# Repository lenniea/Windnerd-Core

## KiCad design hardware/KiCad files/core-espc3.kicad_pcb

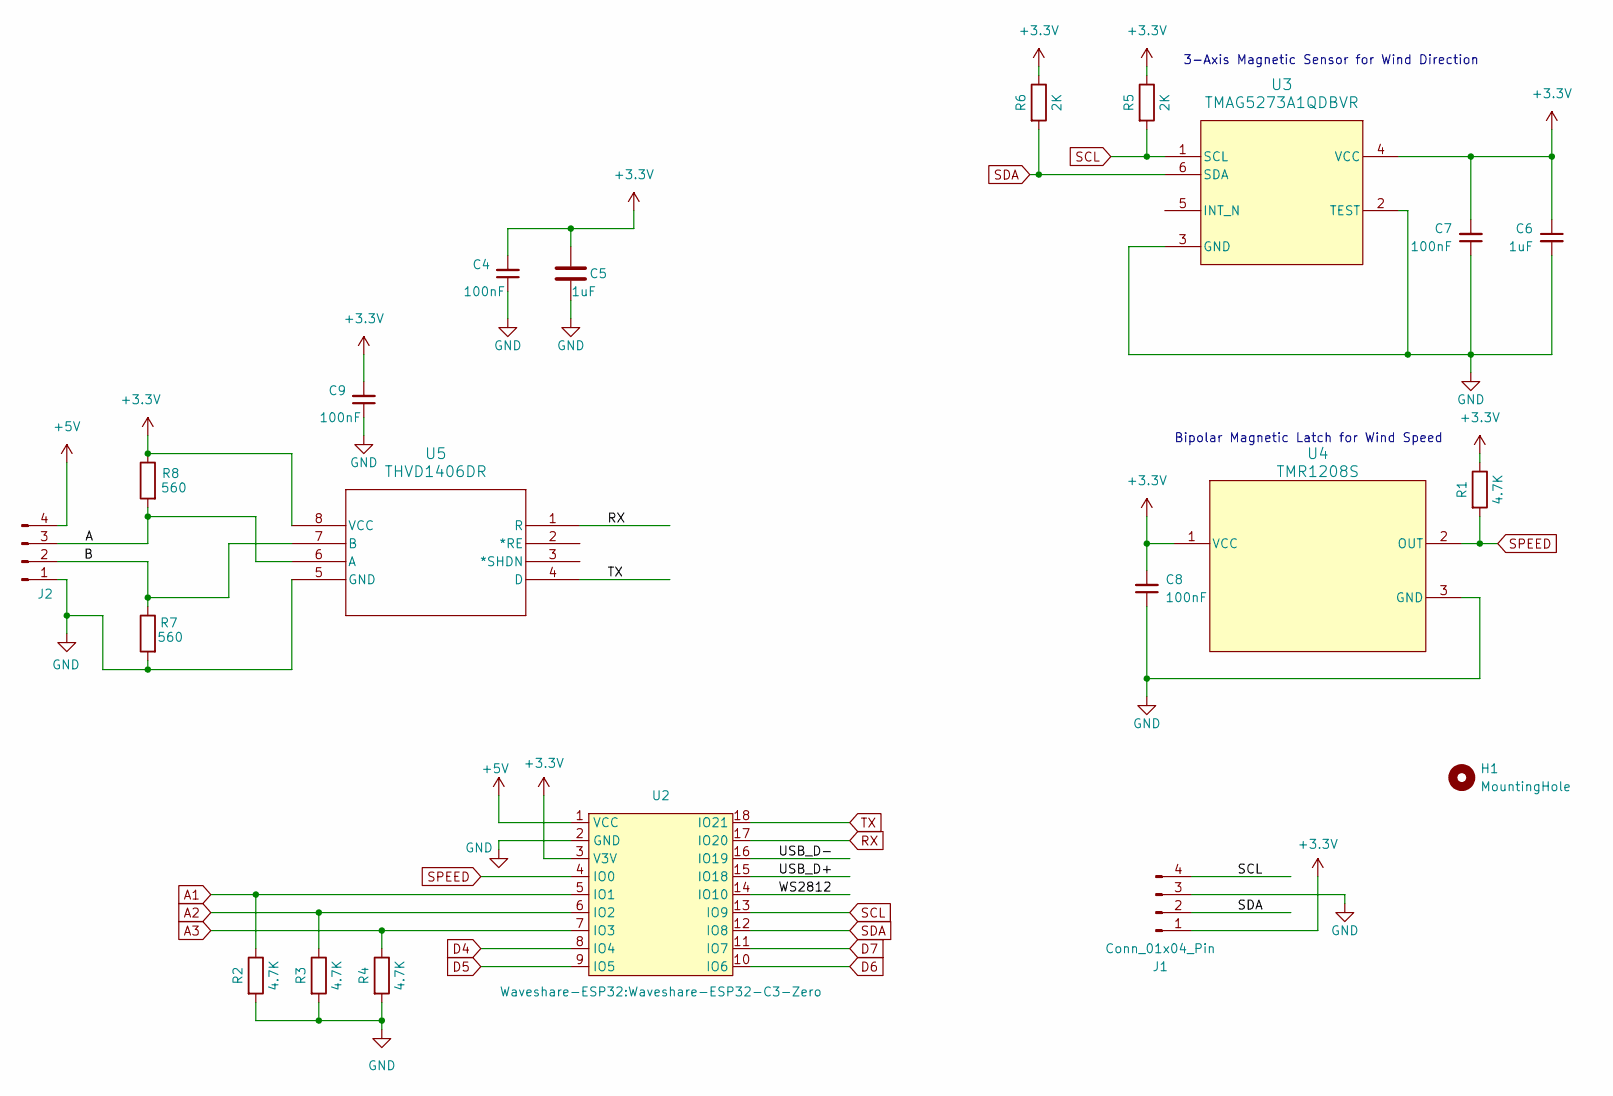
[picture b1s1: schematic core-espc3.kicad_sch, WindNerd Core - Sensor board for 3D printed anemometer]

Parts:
C4, C7, C8, C9: 100nF; C_0603_1608Metric_Pad1.08x0.95mm_HandSolder
C5, C6: 1uF; C_0603_1608Metric_Pad1.08x0.95mm_HandSolder
H1: MountingHole; MountingHole_3.2mm_M3
J1: Conn_01x04_Pin; PinHeader_1x04_P2.54mm_Vertical
J2: Conn_01x04_Pin; PinHeader_1x04_P2.54mm_Horizontal
R1, R2, R3, R4: 4.7K; R_0603_1608Metric_Pad0.98x0.95mm_HandSolder
R5, R6: 2K; R_0603_1608Metric_Pad0.98x0.95mm_HandSolder
R7, R8: 560; R_0603_1608Metric_Pad0.98x0.95mm_HandSolder
U2: Waveshare-ESP32-C3-Zero
U3: TMAG5273A1QDBVR; SOT-23-6
U4: TMR1208S; SOT-23
U5: THVD1406DR; SOIC-8_5.3x6.2mm_P1.27mm

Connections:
+3.3V: C4.2, C5.1, C6.1, C7.2, C8.2, C9.2, J1.1, R1.1, R5.1, R6.1, R8.1, U2.3 (V3V), U3.4 (VCC), U4.1 (VCC), U5.8 (VCC)
+5V: J2.4, U2.1 (VCC)
/A: J2.3, R8.2, U5.6 (A)
/B: J2.2, R7.1, U5.7 (B)
/USB_D+: U2.15 (IO18)
/USB_D-: U2.16 (IO19)
/WS2812: U2.14 (IO10)
A1: R2.1, U2.5 (IO1)
A2: R3.1, U2.6 (IO2)
A3: R4.1, U2.7 (IO3)
D4: U2.8 (IO4)
D5: U2.9 (IO5)
D6: U2.10 (IO6)
D7: U2.11 (IO7)
GND: C4.1, C5.2, C6.2, C7.1, C8.1, C9.1, J1.3, J2.1, R2.2, R3.2, R4.2, R7.2, U2.2 (GND), U3.2 (TEST), U3.3 (GND), U4.3 (GND), U5.5 (GND)
RX: U2.17 (IO20), U5.1 (R)
SCL: J1.4, R5.2, U2.13 (IO9), U3.1 (SCL)
SDA: J1.2, R6.2, U2.12 (IO8), U3.6 (SDA)
SPEED: R1.2, U2.4 (IO0), U4.2 (OUT)
TX: U2.18 (IO21), U5.4 (D)

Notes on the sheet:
3-Axis Magnetic Sensor for Wind Direction
Bipolar Magnetic Latch for Wind Speed

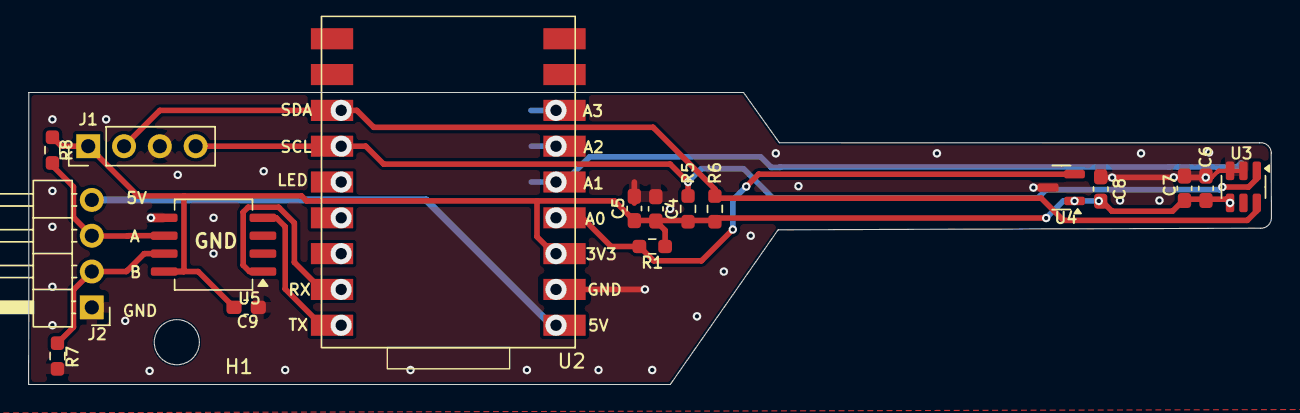
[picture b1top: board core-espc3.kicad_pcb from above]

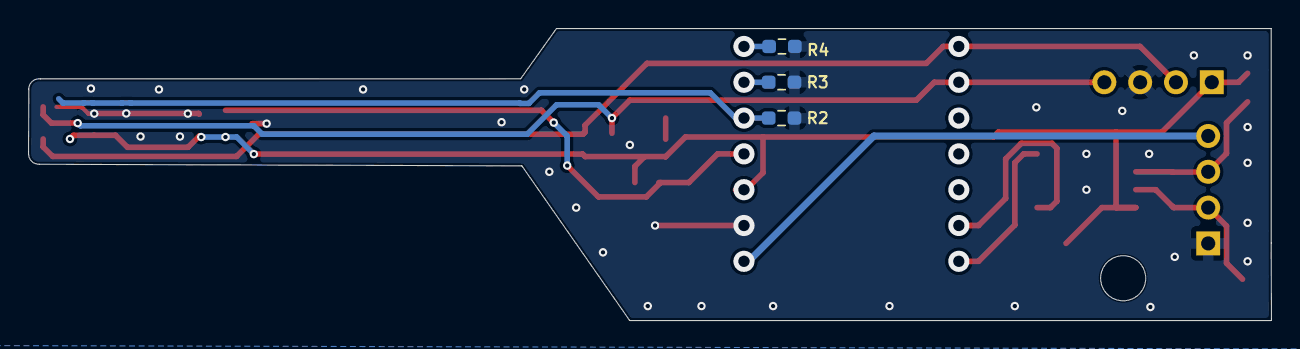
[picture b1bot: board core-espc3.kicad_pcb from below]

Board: 2 copper layers, 88.2 x 20.7 mm, 21 parts (3 on the bottom side), 13 nets.

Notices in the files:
hardware/KiCad files/core-espc3.kicad_pcb:
Copyright (c) 2025 windnerd.net
Licensed under CERN Open Hardware License V2 – Strongly Reciprocal (CERN-OHL-S)
